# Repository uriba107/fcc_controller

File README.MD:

## FCC3 controller board
This Arduino Based project, is meant to allow FCC3 force sensing mod for Cougar, to be used with Thrustmaster Warthog without the need to use the old TM Cougar Electronics

This software is distributed under MIT license, and is provided as is and without any warranty what so ever. Further information can be found in "license.txt" which belongs to the LUFA framework on which controller code is based.

### Table Of Content
- [FCC3 controller board](#fcc3-controller-board)
  - [Features](#features)
  - [What settings are recommended](#what-settings-are-recommended)
  - [FLCS in F-16](#flcs-in-f-16)
      - [Analog FLCS](#analog-flcs)
      - [Digital FLCS](#digital-flcs)
  - [Cheat sheet](#cheat-sheet)
  - [BOM](#bom)

### Features
  * 11 bit output on Pitch and Roll.
  * Support for both Cougar and Warthog grips.
  * On the fly configuration changes:
    * Multiple force presets (9, 6 & 4.5 Kg/f), in addition to one user configurable sensitivity setting.
    * User toggleable, FLCS Based, realistic force ratios.  
    * User toggleable FLCS sensor rotation. In later blocks, the stick sensor is rotated clockwise to reduce accidental roll on pitch commands. Activating this option will simulate that.
    * on the fly re-centering (just in case).
  * Bi-Directional Control software:
    * Allows Joystick settings change (same as available via the grip).
    * Allows User configurable sensitivity setting to be set.
    * Handles Firmware upgrades for the stick.
    
**Note:** <br>
The code was developed with the help of ViperCore, makers of the FCC3. They have also produce a compatible board which can be purchsed either as a [Standalone board](http://www.vipercore.nl/index.php/webshop/view/productdetails/virtuemart_product_id/58/virtuemart_category_id/14) or [bundled with FCW1 module](http://www.vipercore.nl/index.php/webshop/view/productdetails/virtuemart_product_id/56/virtuemart_category_id/14)

### What settings are recommended
  FLCS and SSC config had changed over the years, so depending on what type of F-16 you want to model, settings will vary.

<b><u><i> Blocks 30/32 and before: </b></u></i>
  * Analog FLCS
  * Sensor Rotation -  Disabled

<b><u><i> Block 40/42 and after: </b></u></i>
  * Digital FLCS
  * Sensor Rotation - Enabled

### FLCS in F-16
There are two types of FLCS installed in F-16s.The controller attempts to emulate both system operational logic.</br>

In both cases, force ratio is maintained by the controller. The selected force setting is used as full pitch up command (which is the maximum required force), while pitch down and roll are proportional according to the FLCS version emulated.

#### Analog FLCS
  <b>Real life:</b><br>
   Full pitch up command is 180N (about 18Kgf), while full pitch down and full roll are 80N (or about 8Kgf).

  <b>Controller example:</b> in 9Kg/f mode, full pitch up will be 9kg/f for full deflection, but on the other axis, only 4kg/f will be required.

#### Digital FLCS
  <b>Real life:</b><br>
  full pitch up command is 25lbf, while full pitch down is 16lbf and full roll is 17lbf.

  <b>Controller example:</b><br>
  In 9kgf mode, Pitch up command will be  9kgf for full deflection. full pitch down will require 5.76kgf and full roll will require 6.12kgf.

### Cheat sheet

### BOM
* Atmega 32U4 based board ([Arduino pro-micro](http://www.ebay.com/sch/i.html?_from=R40&_trksid=p2050601.m570.l1313.TR0.TRC0.H0.Xarduino+pro-micro.TRS0&_nkw=arduino+pro-micro&_sacat=0) or an [Arduino Micro](https://www.arduino.cc/en/Main/arduinoBoardMicro) are recommended)
* [MCP3202](http://www.ebay.com/sch/i.html?_odkw=arduino+pro-micro&_osacat=0&_from=R40&_trksid=p2045573.m570.l1313.TR0.TRC0.H0.XMCP3202.TRS0&_nkw=MCP3202&_sacat=0) - 12 Bit external ADC
* A small protoboard (cheap dual sided 4*6 will be good enough)
* For Pro-micro - A momentary push button and 10+ Kohm resistor as the board has no reset switch.
* A few LEDs and resistors - for status.
* Header pins, two 3 pin headers and one 5 pins header, for grip and analog sensors. Generic 0.1" headers will do the trick. But correct header will be the [ JST EH series connectors](http://www.jst-belgium.be/productSeries.php?pid=46).
* Female Headers for the Arduino (optional)
* DIP8 socket for the MCP3202 (optional)

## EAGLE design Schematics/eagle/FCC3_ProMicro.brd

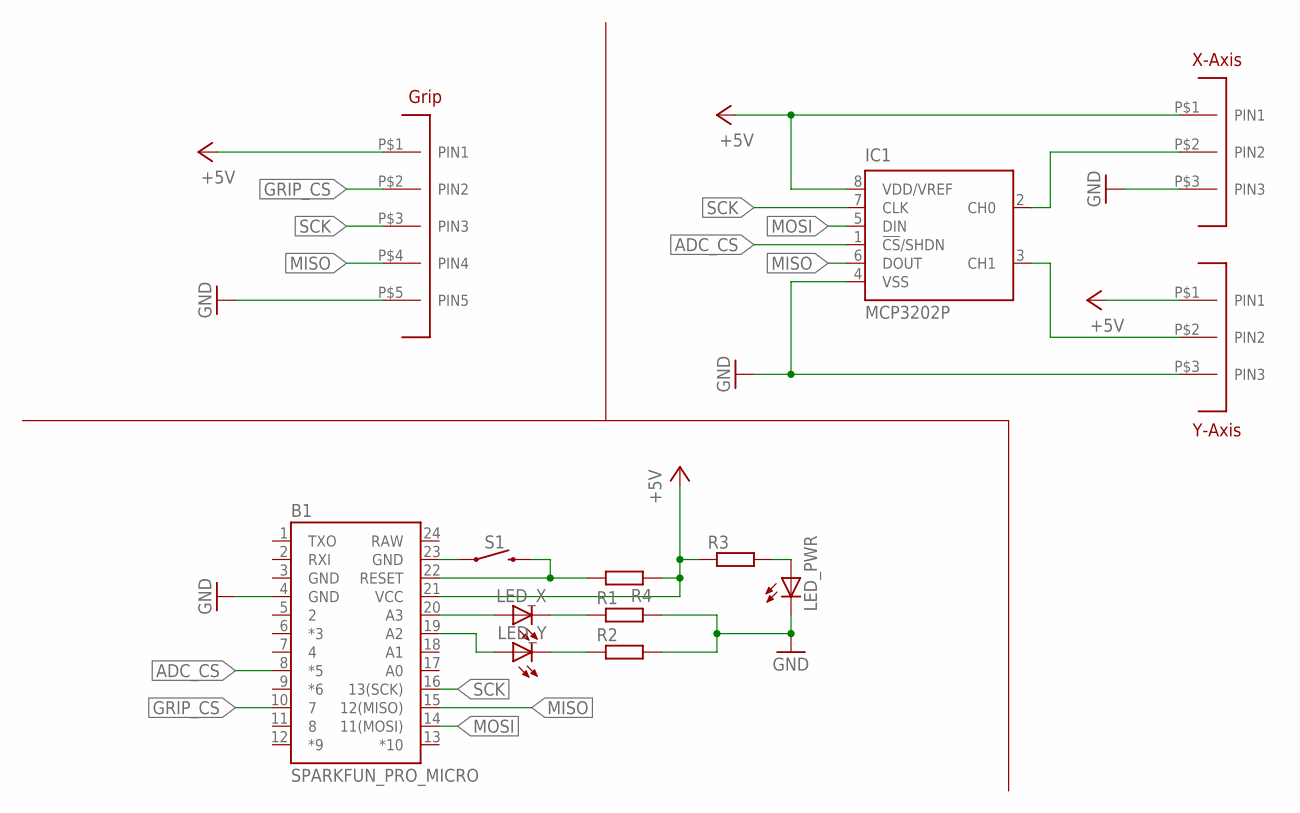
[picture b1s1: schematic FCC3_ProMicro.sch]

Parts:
B1: SPARKFUN_PRO_MICRO
IC1: MCP3202P; DIL8
LED_PWR: LED3MM
LED_X: LED3MM
LED_Y: LED3MM
R1, R2, R3, R4: R-EU_0204/5; 0204/5
S1: MOMENTARY-SWITCH-SPST-PTH-6.0MM; TACTILE_SWITCH_PTH_6.0MM
U$1, U$2: JST_EH_3PIN; JST-EH-3PIN
U$3: JST_EH_5PIN; JST-EH-5PIN

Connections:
+5V: B1.21 (VCC), IC1.8 (VDD/VREF), R3.1, R4.1, U$1.P$1 (PIN1), U$2.P$1 (PIN1), U$3.P$1 (PIN1)
ADC_CS: B1.8 (*5), IC1.1 (!CS!/SHDN)
GND: B1.3 (GND), B1.4 (GND), B1.23 (GND), IC1.4 (VSS), LED_PWR.K (C), R1.2, R2.2, S1.1, U$1.P$3 (PIN3), U$2.P$3 (PIN3), U$3.P$5 (PIN5)
GRIP_CS: B1.10 (7), U$3.P$2 (PIN2)
MISO: B1.15 (12(MISO)), IC1.6 (DOUT), U$3.P$4 (PIN4)
MOSI: B1.14 (11(MOSI)), IC1.5 (DIN)
unnamed: IC1.2 (CH0), U$2.P$2 (PIN2)
unnamed: IC1.3 (CH1), U$1.P$2 (PIN2)
unnamed: B1.20 (A3), LED_X.A
unnamed: B1.19 (A2), LED_Y.A
unnamed: LED_PWR.A, R3.2
unnamed: LED_Y.K (C), R2.1
unnamed: LED_X.K (C), R1.1
RAW: B1.24 (RAW)
RESET: B1.22 (RESET), R4.2, S1.3 (2)
SCK: B1.16 (13(SCK)), IC1.7 (CLK), U$3.P$3 (PIN3)

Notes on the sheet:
Grip
X-Axis
Y-Axis

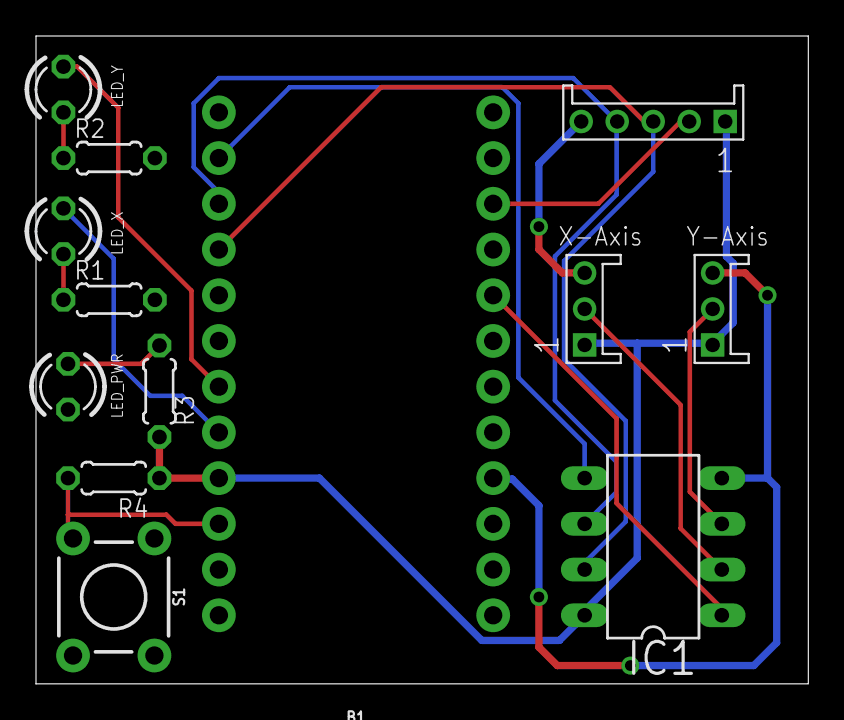
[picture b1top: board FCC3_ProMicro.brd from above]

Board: 2 copper layers, 42.9 x 36.0 mm, 13 parts (0 on the bottom side), 15 nets.

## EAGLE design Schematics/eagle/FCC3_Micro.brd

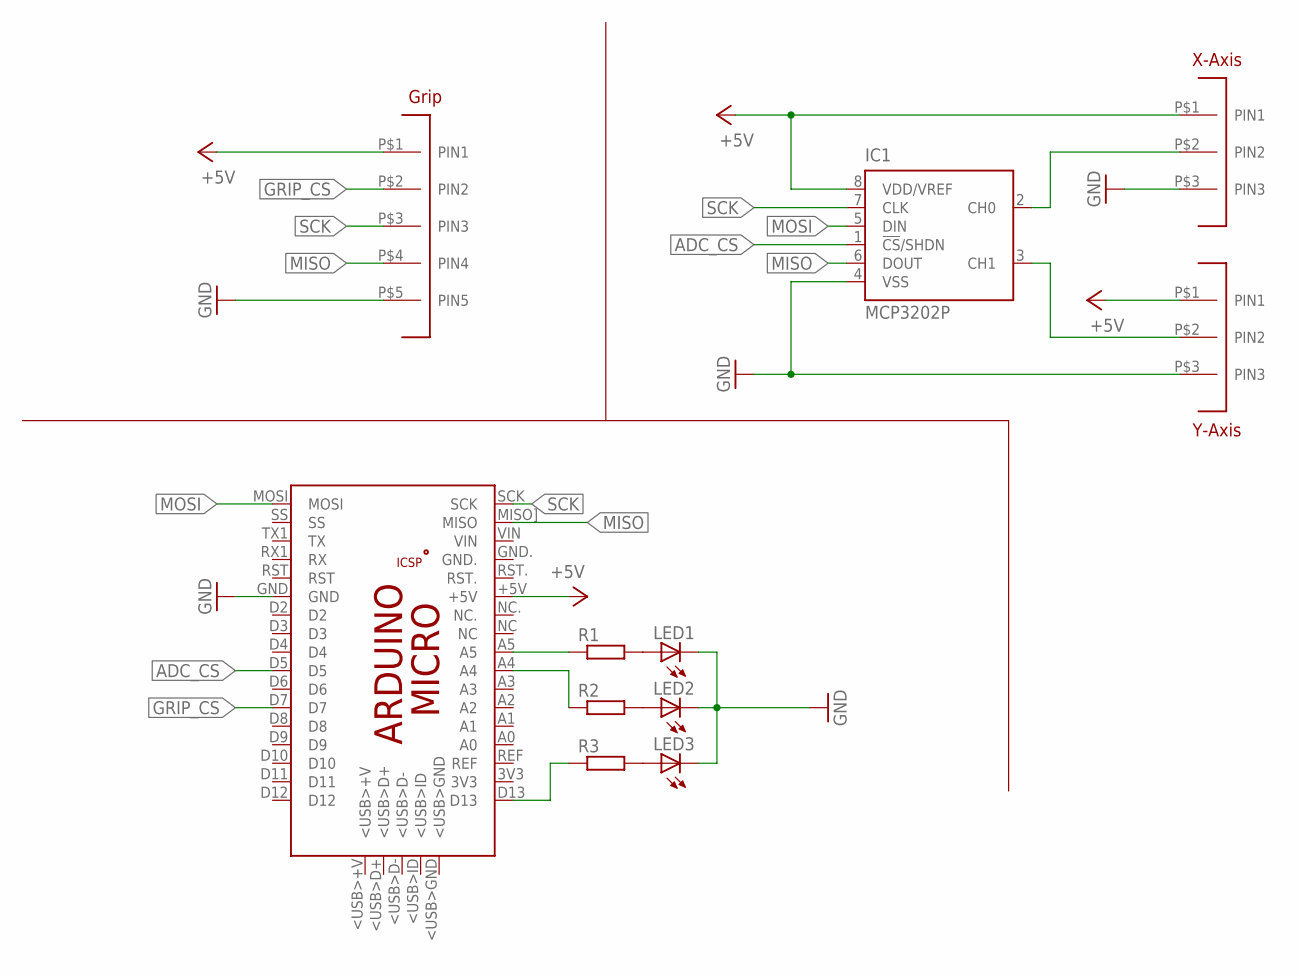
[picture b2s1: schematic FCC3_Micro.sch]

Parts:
IC1: MCP3202P; DIL8
LED1, LED2, LED3: LED5MM
PCB1: ARDUINO_MICRO
R1, R2, R3: R-EU_0204/5; 0204/5
U$1, U$2: JST_EH_3PIN; JST-EH-3PIN
U$3: JST_EH_5PIN; JST-EH-5PIN

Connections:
+5V: IC1.8 (VDD/VREF), PCB1.+5V, U$1.P$1 (PIN1), U$2.P$1 (PIN1), U$3.P$1 (PIN1)
ADC_CS: IC1.1 (!CS!/SHDN), PCB1.D5
GND: IC1.4 (VSS), LED1.K (C), LED2.K (C), LED3.K (C), PCB1.GND, U$1.P$3 (PIN3), U$2.P$3 (PIN3), U$3.P$5 (PIN5)
GRIP_CS: PCB1.D7, U$3.P$2 (PIN2)
MISO: IC1.6 (DOUT), PCB1.MISO] (MISO), U$3.P$4 (PIN4)
MOSI: IC1.5 (DIN), PCB1.MOSI
unnamed: IC1.2 (CH0), U$2.P$2 (PIN2)
unnamed: IC1.3 (CH1), U$1.P$2 (PIN2)
unnamed: LED3.A, R3.2
unnamed: LED1.A, R1.2
unnamed: LED2.A, R2.2
SCK: IC1.7 (CLK), PCB1.SCK, U$3.P$3 (PIN3)
STATUS: PCB1.D13, R3.1
X-LED: PCB1.A5, R1.1
Y-LED: PCB1.A4, R2.1

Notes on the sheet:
Grip
X-Axis
Y-Axis

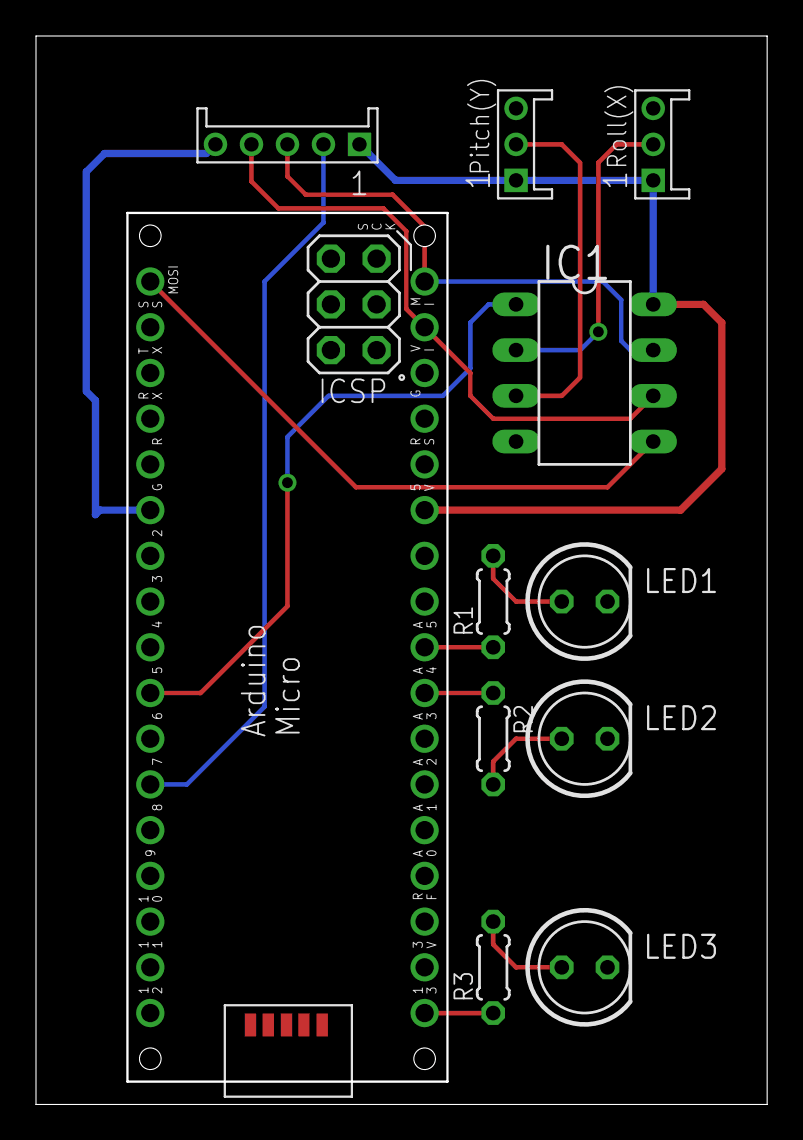
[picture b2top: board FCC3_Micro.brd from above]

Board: 2 copper layers, 40.6 x 59.4 mm, 11 parts (0 on the bottom side), 15 nets.

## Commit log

2017-03-16 added readme
2017-03-16 add license
2017-03-16 change poll reate to 4ms, reprisenting 250Hz
2017-03-20 HID Output mode added.
2017-03-24 Added remote configuration
2017-03-25 App initial commit
2017-03-25 Added Micro/Pro-Micro schematics and boards
2017-03-25 clean up
2017-03-25 New PID
    Cleanup some old functions as well.
2017-03-29 added license file
2017-04-01 App version 0.1.3.2 slight rewrite + installer
2017-04-01 Firmware 0.1.3 New PID and some better comms with PC software
2017-04-02 fix CTD when no internet connection is present
2017-04-06 Add support for FCC revision gains
2017-04-06 FW 0.1.4 - FCC gains selector
2017-04-08 replace force mapping with Analog/Digital FLCS
2017-04-10 replace "center" button with "read settings"
2017-04-11 moved buttons around
2017-05-05 Version 1.0.0
2017-05-06 Update README.MD
    fix bold
2017-05-18 Slightly larger deadzone
2017-05-18 Add "Test Joystick" display
2017-08-13 add graphical joystick tracker and bugfixes
2017-08-13 new deadzone logic
2017-12-18 button layout image
2017-12-18 tweaks to readme
2018-01-05 Potential fix for EEPROM loading issue
2018-01-06 Update README.MD
    Added linkes to VipeCore website for a complete product
2018-05-29 Attempt to Fix EEPROM loading Upgrade LUFA to 170418
2019-09-30 added original FCC3 manuals and documentations as dowloaded from vipercore.nl Arend "WhiteEagle" creator of FCC3 has past away and I wanted to keep these manuals available as the website might go down
2021-10-25 add isChanged logic
2021-10-25 change config mode to 3 seconds

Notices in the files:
parts and their libraries:
SparkFun-Boards: Licensing: Creative Commons ShareAlike 4.0 International - https://creativecommons.org/licenses/by-sa/4.0
